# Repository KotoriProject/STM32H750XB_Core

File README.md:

# STM32 H750XBH6 核心板设计规划
## 设计理念
从STM32的F0、F1系列一路至今，到目前最为复杂的H750IBK6开发板、核心板的设计，逐渐认识到了单片机系统的设计思路。

在使用低性能单片机的情况下，通常最小系统的PCB layout只需要普通的两层即可。因此，在这种情况下，应当尽量采用**一体化设计**，既可以节省PCB成本，又无需考虑多个PCB之间的耦合设计。

但如果使用的是像H7这一类的**高性能芯片**，并且，这些芯片因为其封装、外部扩展ram等等，会导致最小系统的复杂度急剧提升，PCB layout通常都需要**4层甚至以上的设计**，此时，如果还像低性能单片机一样一体化设计，将核心系统和外围系统设计到一个PCB上，不仅会无故增加成本，并且每一个不同的项目需求的外围电路不尽相同，若更改外围电路则需要连同核心系统一起更改，将会**花费大量时间在重复设计核心系统上**。

因此，采用核心板+底板的设计方式应运而生。通过将核心系统单独设计成一块固定的PCB，并通过引出**具有通用性的接口**，可以使得核心系统**随意**搭配不同的底板（外围电路）。
## 设计目标
1. 通过设计该核心板和对应配套的底板，在实践中学习到相应的知识。
2. 设计出一款可以使用核心芯片所具有的广泛的外设接口、并核心自身又有搭载必要的**内存拓展空间**。
3. 利用设计出的核心板和底板，实现各种个人构想的项目。

## 硬件设计
### Power
参考ST官方给出的H7电源设计，STM32H750XBH6共有以下供电域：

1. dw
2. 123
3. 321
4. 313421414
5. 
123321414
### External Memory
### GPIO AFIO
### Debug Port
### Physical Port

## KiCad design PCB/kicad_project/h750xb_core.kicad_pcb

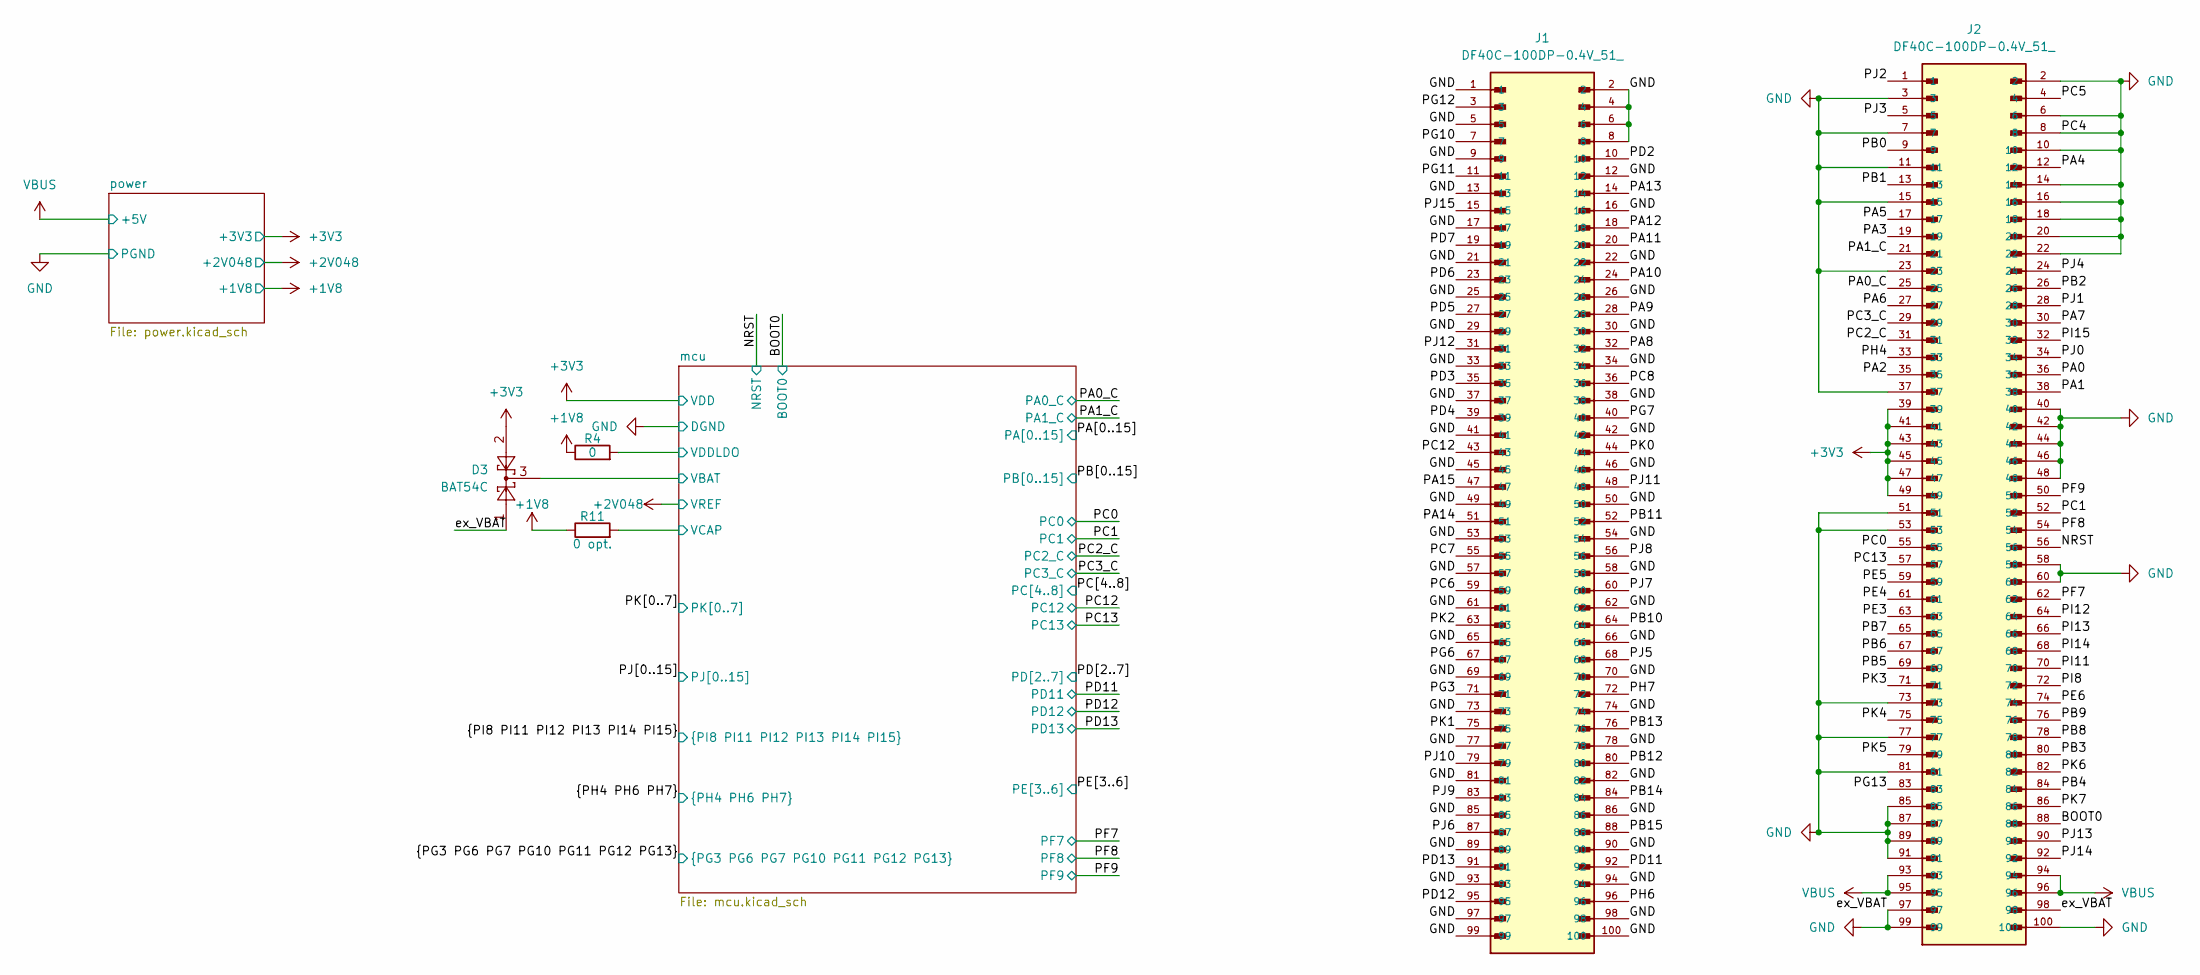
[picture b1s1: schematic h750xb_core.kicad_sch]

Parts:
D3: BAT54C; SOT-23
J1, J2: DF40C-100DP-0.4V_51_; HIROSE_DF40C-100DP-0.4V_51_; PARTREV 8
R4: 0; R_0603_1608Metric
R11: 0 opt.; R_0603_1608Metric

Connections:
+1V8: R4.1, R11.1; also elsewhere on the board
+3V3: D3.2, J2.39, J2.41, J2.43, J2.45, J2.47, J2.49; also elsewhere on the board
/BOOT0: J2.88; also elsewhere on the board
/NRST: J2.56; also elsewhere on the board
/PA0: J2.36; also elsewhere on the board
/PA0_C: J2.25; also elsewhere on the board
/PA1: J2.38; also elsewhere on the board
/PA1_C: J2.21; also elsewhere on the board
/PA2: J2.35; also elsewhere on the board
/PA3: J2.19; also elsewhere on the board
/PA4: J2.12; also elsewhere on the board
/PA5: J2.17; also elsewhere on the board
/PA6: J2.27; also elsewhere on the board
/PA7: J2.30; also elsewhere on the board
/PA8: J1.32; also elsewhere on the board
/PA9: J1.28; also elsewhere on the board
/PA10: J1.24; also elsewhere on the board
/PA11: J1.20; also elsewhere on the board
/PA12: J1.18; also elsewhere on the board
/PA13: J1.14; also elsewhere on the board
/PA14: J1.51; also elsewhere on the board
/PA15: J1.47; also elsewhere on the board
/PB0: J2.9; also elsewhere on the board
/PB1: J2.13; also elsewhere on the board
/PB2: J2.26; also elsewhere on the board
/PB3: J2.80; also elsewhere on the board
/PB4: J2.84; also elsewhere on the board
/PB5: J2.69; also elsewhere on the board
/PB6: J2.67; also elsewhere on the board
/PB7: J2.65; also elsewhere on the board
/PB8: J2.78; also elsewhere on the board
/PB9: J2.76; also elsewhere on the board
/PB10: J1.64; also elsewhere on the board
/PB11: J1.52; also elsewhere on the board
/PB12: J1.80; also elsewhere on the board
/PB13: J1.76; also elsewhere on the board
/PB14: J1.84; also elsewhere on the board
/PB15: J1.88; also elsewhere on the board
/PC0: J2.55; also elsewhere on the board
/PC1: J2.52; also elsewhere on the board
/PC2_C: J2.31; also elsewhere on the board
/PC3_C: J2.29; also elsewhere on the board
/PC5: J2.4; also elsewhere on the board
/PC6: J1.59; also elsewhere on the board
/PC7: J1.55; also elsewhere on the board
/PC8: J1.36; also elsewhere on the board
/PC12: J1.43; also elsewhere on the board
/PC13: J2.57; also elsewhere on the board
/PD2: J1.10; also elsewhere on the board
/PD3: J1.35; also elsewhere on the board
/PD4: J1.39; also elsewhere on the board
/PD5: J1.27; also elsewhere on the board
/PD6: J1.23; also elsewhere on the board
/PD7: J1.19; also elsewhere on the board
/PD11: J1.92; also elsewhere on the board
/PD12: J1.95; also elsewhere on the board
/PD13: J1.91; also elsewhere on the board
/PE3: J2.63; also elsewhere on the board
/PE4: J2.61; also elsewhere on the board
/PE5: J2.59; also elsewhere on the board
/PE6: J2.74; also elsewhere on the board
/PF7: J2.62; also elsewhere on the board
/PF8: J2.54; also elsewhere on the board
/PF9: J2.50; also elsewhere on the board
/PG3: J1.71; also elsewhere on the board
/PG6: J1.67; also elsewhere on the board
/PG7: J1.40; also elsewhere on the board
/PG10: J1.7; also elsewhere on the board
/PG11: J1.11; also elsewhere on the board
/PG12: J1.3; also elsewhere on the board
/PG13: J2.83; also elsewhere on the board
/PH4: J2.33; also elsewhere on the board
/PH6: J1.96; also elsewhere on the board
/PH7: J1.72; also elsewhere on the board
/PI8: J2.72; also elsewhere on the board
/PI11: J2.70; also elsewhere on the board
/PI12: J2.64; also elsewhere on the board
/PI13: J2.66; also elsewhere on the board
/PI14: J2.68; also elsewhere on the board
/PI15: J2.32; also elsewhere on the board
/PJ0: J2.34; also elsewhere on the board
/PJ1: J2.28; also elsewhere on the board
/PJ2: J2.1; also elsewhere on the board
/PJ3: J2.5; also elsewhere on the board
/PJ4: J2.24; also elsewhere on the board
/PJ5: J1.68; also elsewhere on the board
/PJ6: J1.87; also elsewhere on the board
/PJ7: J1.60; also elsewhere on the board
/PJ8: J1.56; also elsewhere on the board
/PJ9: J1.83; also elsewhere on the board
/PJ10: J1.79; also elsewhere on the board
/PJ11: J1.48; also elsewhere on the board
/PJ12: J1.31; also elsewhere on the board
/PJ13: J2.90; also elsewhere on the board
/PJ14: J2.92; also elsewhere on the board
/PJ15: J1.15; also elsewhere on the board
/PK0: J1.44; also elsewhere on the board
/PK1: J1.75; also elsewhere on the board
/PK2: J1.63; also elsewhere on the board
/PK3: J2.71; also elsewhere on the board
/PK4: J2.75; also elsewhere on the board
/PK5: J2.79; also elsewhere on the board
/PK6: J2.82; also elsewhere on the board
/PK7: J2.86; also elsewhere on the board
/mcu/VBAT: D3.3; also elsewhere on the board
/mcu/VCAP: R11.2; also elsewhere on the board
/mcu/VDDLDO: R4.2; also elsewhere on the board
GND: D3.1, J1.1, J1.2, J1.4, J1.5, J1.6, J1.8, J1.9, J1.12, J1.13, J1.16, J1.17, J1.21, J1.22, J1.25, J1.26, J1.29, J1.30, J1.33, J1.34, J1.37, J1.38, J1.41, J1.42, J1.45, J1.46, J1.49, J1.50, J1.53, J1.54, J1.57, J1.58, J1.61, J1.62, J1.65, J1.66, J1.69, J1.70, J1.73, J1.74, J1.77, J1.78, J1.81, J1.82, J1.85, J1.86, J1.89, J1.90, J1.93, J1.94, J1.97, J1.98, J1.99, J1.100, J2.2, J2.3, J2.6, J2.7, J2.8, J2.10, J2.11, J2.14, J2.15, J2.16, J2.18, J2.20, J2.22, J2.23, J2.37, J2.40, J2.42, J2.44, J2.46, J2.48, J2.51, J2.53, J2.58, J2.60, J2.73, J2.77, J2.81, J2.85, J2.87, J2.89, J2.91, J2.97, J2.98, J2.99, J2.100; also elsewhere on the board
VBUS: J2.93, J2.94, J2.95, J2.96; also elsewhere on the board

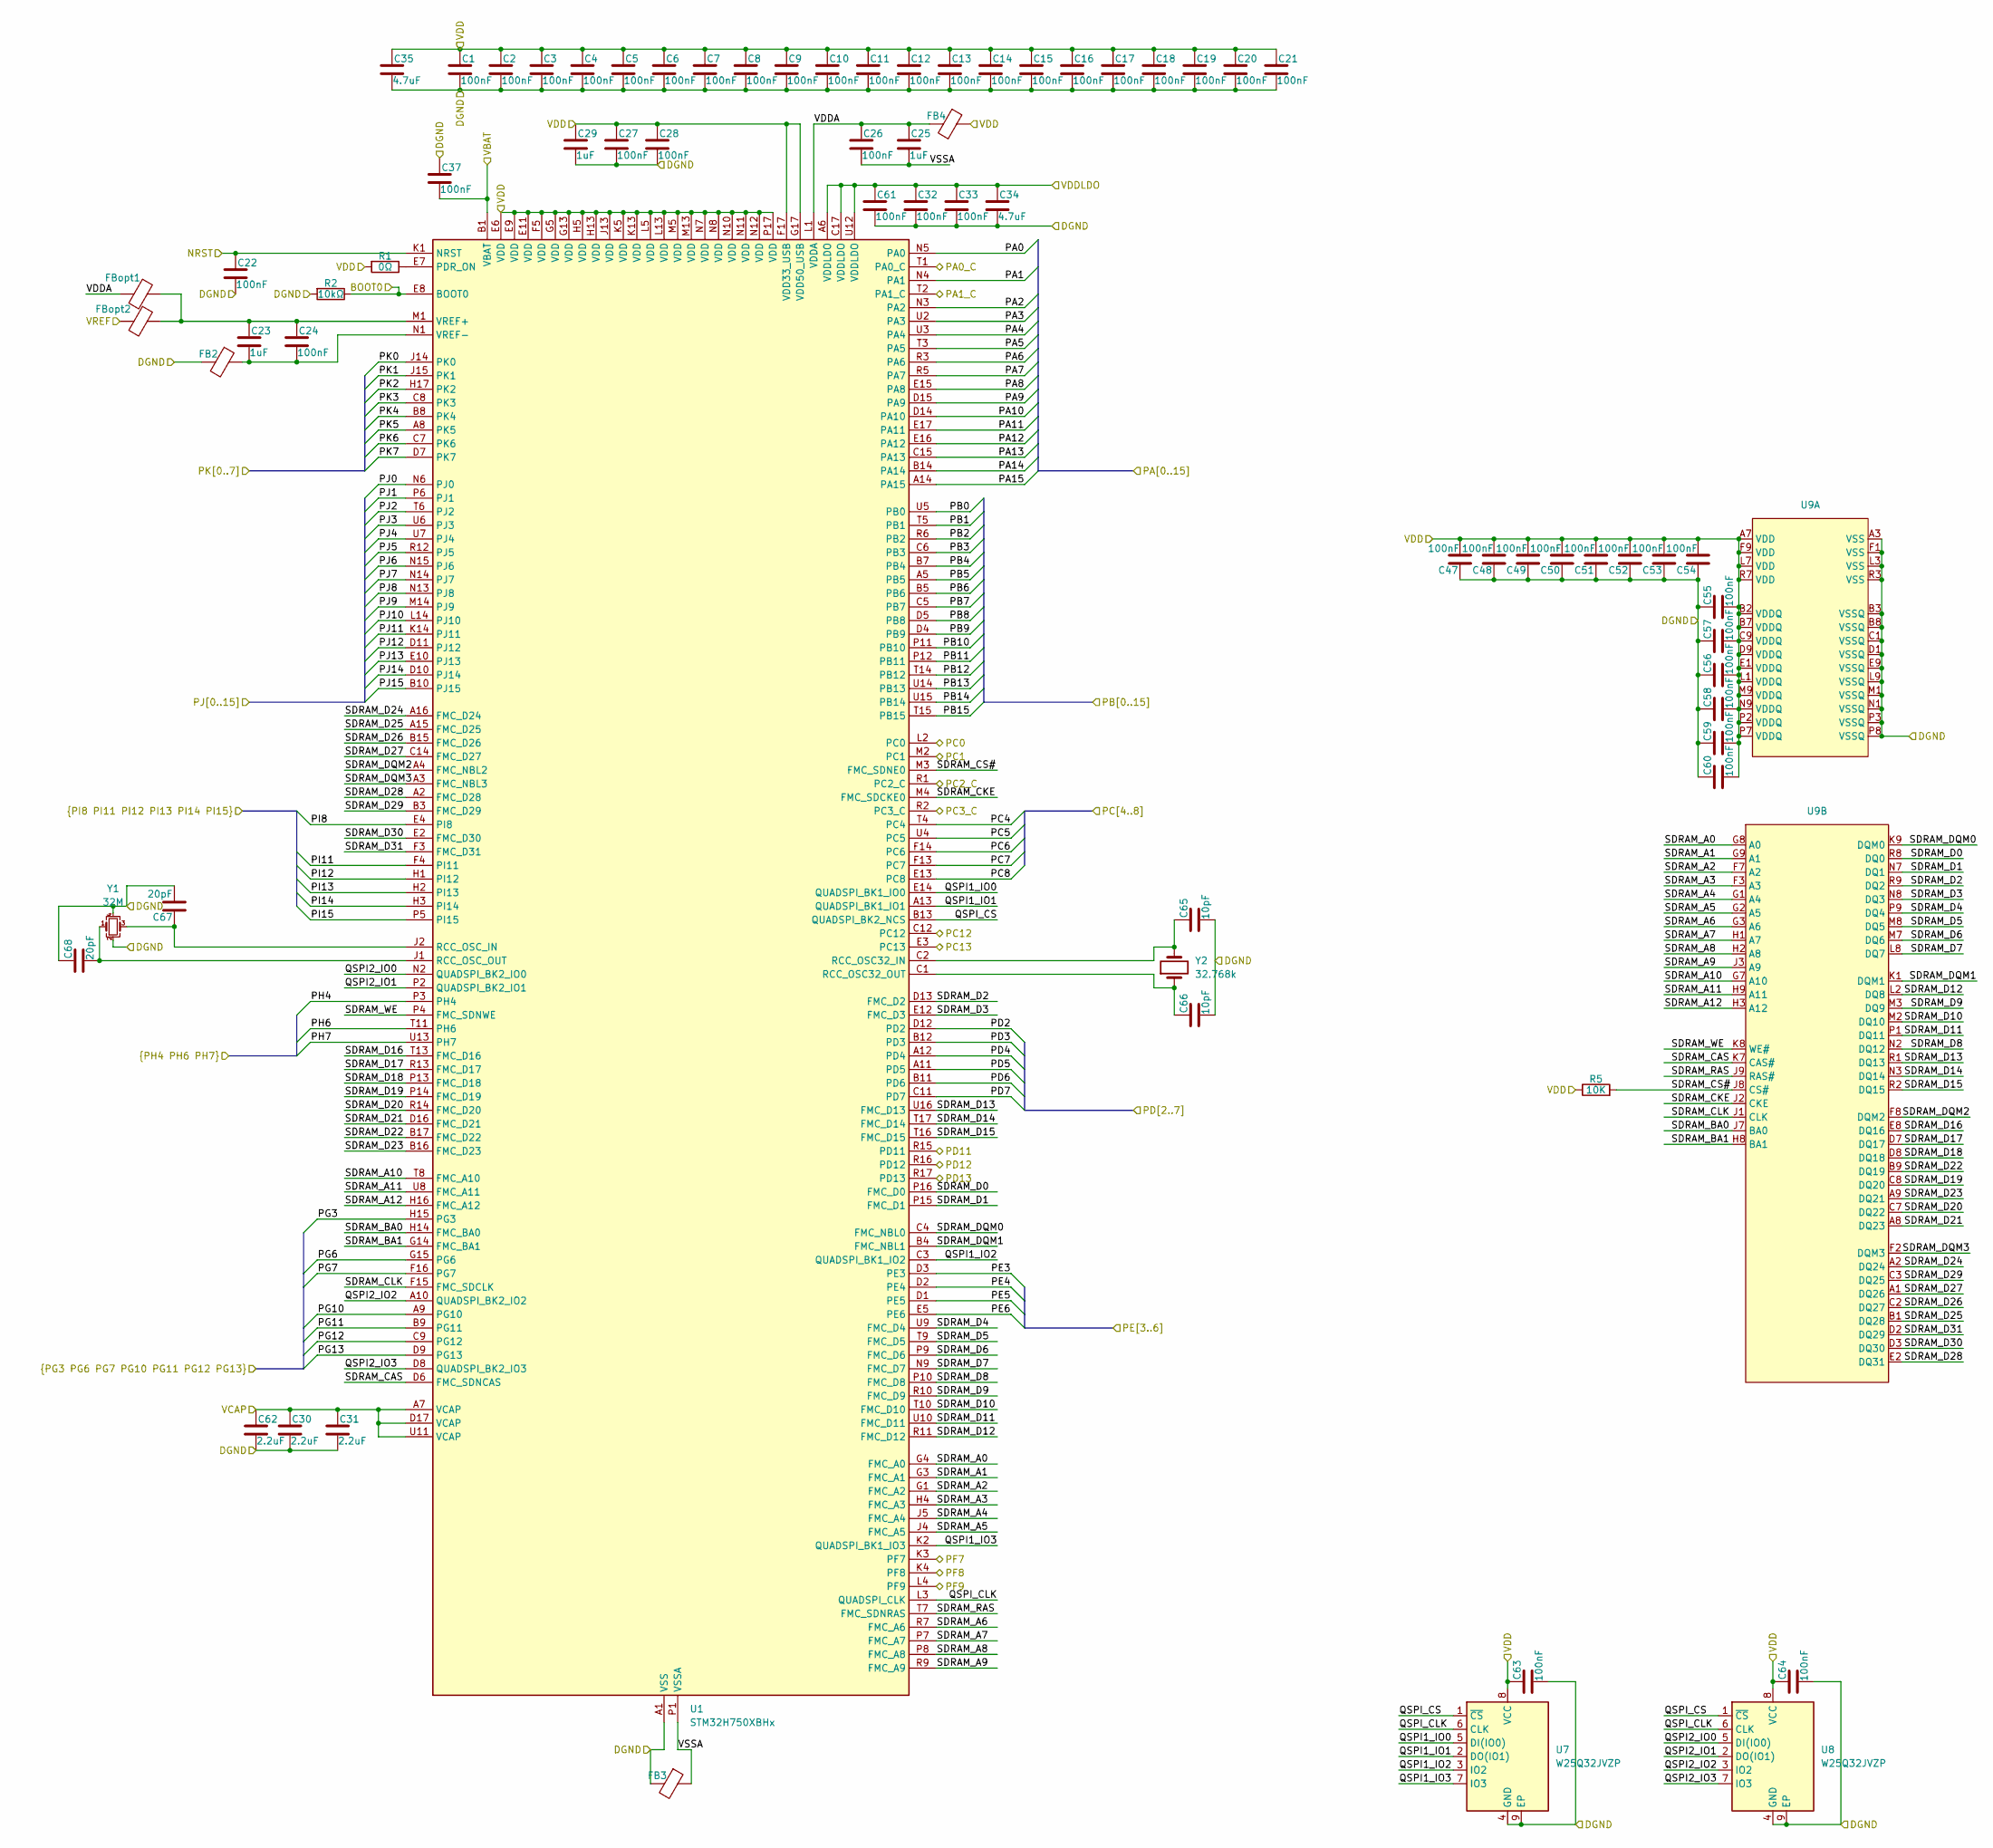
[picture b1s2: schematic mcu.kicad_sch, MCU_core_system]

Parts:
C1, C3, C4, C5, C6, C7, C8, C9, C10, C11, C12, C13, C14, C15, C17, C18, C19, C20, C21: 100nF; C_0201_0603Metric_Pad0.64x0.40mm_HandSolder
C2, C16, C22, C24, C26, C27, C28, C32, C33, C37, C47, C48, C49, C50, C51, C52, C53, C54, C55, C56, C57, C58, C59, C60, C61, C63, C64: 100nF; C_0402_1005Metric
C23, C25, C29: 1uF; C_0402_1005Metric
C30, C31, C62: 2.2uF; C_0402_1005Metric
C34, C35: 4.7uF; C_0402_1005Metric
C65, C66: 10pF; C_0402_1005Metric
C67, C68: 20pF; C_0402_1005Metric
FB2, FB3, FB4: 120Ω; L_0603_1608Metric; LCSC C14709
FBopt1, FBopt2: 120Ω; L_0603_1608Metric; LCSC C14709
R1: 0Ω; R_0402_1005Metric
R2: 10kΩ; R_0402_1005Metric
R5: 10K; R_0402_1005Metric
U1: STM32H750XBHx; TFBGA-265_14x14mm_Layout17x17_P0.8mm
U7, U8: W25Q32JVZP; WSON-8-1EP_6x5mm_P1.27mm_EP3.4x4.3mm
U9: BGA-90_8.0x13.0mm_Layout2x3x15_P0.8mm; Manufacturer Part IS42S32160F-7BLI; LCSC Part Name IS42S32160F-7BLI
Y1: 32M; Crystal_SMD_2016-4Pin_2.0x1.6mm; LCSC C2965582
Y2: 32.768k; Crystal_SMD_3215-2Pin_3.2x1.5mm; LCSC C48615

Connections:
+2V048: FBopt2.2; also elsewhere on the board
+3V3: C1.1, C2.1, C3.1, C4.1, C5.1, C6.1, C7.1, C8.1, C9.1, C10.1, C11.1, C12.1, C13.1, C14.1, C15.1, C16.1, C17.1, C18.1, C19.1, C20.1, C21.1, C27.1, C28.1, C29.1, C35.1, C47.2, C48.2, C49.2, C50.2, C51.2, C52.2, C53.2, C54.2, C55.2, C56.2, C57.2, C58.2, C59.2, C60.2, C63.1, C64.1, FB4.1, R1.2, R5.1, U1.E6 (VDD), U1.E9 (VDD), U1.E11 (VDD), U1.F5 (VDD), U1.F17 (VDD33_USB), U1.G5 (VDD), U1.G13 (VDD), U1.G17 (VDD50_USB), U1.H5 (VDD), U1.H13 (VDD), U1.J13 (VDD), U1.K5 (VDD), U1.K13 (VDD), U1.L5 (VDD), U1.L13 (VDD), U1.M5 (VDD), U1.M13 (VDD), U1.N7 (VDD), U1.N8 (VDD), U1.N10 (VDD), U1.N11 (VDD), U1.N12 (VDD), U1.P17 (VDD), U7.8 (VCC), U8.8 (VCC), U9.A7 (VDD), U9.B2 (VDDQ), U9.B7 (VDDQ), U9.C9 (VDDQ), U9.D9 (VDDQ), U9.E1 (VDDQ), U9.F9 (VDD), U9.L1 (VDDQ), U9.L7 (VDD), U9.M9 (VDDQ), U9.N9 (VDDQ), U9.P2 (VDDQ), U9.P7 (VDDQ), U9.R7 (VDD); also elsewhere on the board
/BOOT0: R2.1, U1.E8 (BOOT0); also elsewhere on the board
/NRST: C22.1, U1.K1 (NRST); also elsewhere on the board
/PA0: U1.N5 (PA0); also elsewhere on the board
/PA0_C: U1.T1 (PA0_C); also elsewhere on the board
/PA1: U1.N4 (PA1); also elsewhere on the board
/PA1_C: U1.T2 (PA1_C); also elsewhere on the board
/PA2: U1.N3 (PA2); also elsewhere on the board
/PA3: U1.U2 (PA3); also elsewhere on the board
/PA4: U1.U3 (PA4); also elsewhere on the board
/PA5: U1.T3 (PA5); also elsewhere on the board
/PA6: U1.R3 (PA6); also elsewhere on the board
/PA7: U1.R5 (PA7); also elsewhere on the board
/PA8: U1.E15 (PA8); also elsewhere on the board
/PA9: U1.D15 (PA9); also elsewhere on the board
/PA10: U1.D14 (PA10); also elsewhere on the board
/PA11: U1.E17 (PA11); also elsewhere on the board
/PA12: U1.E16 (PA12); also elsewhere on the board
/PA13: U1.C15 (PA13); also elsewhere on the board
/PA14: U1.B14 (PA14); also elsewhere on the board
/PA15: U1.A14 (PA15); also elsewhere on the board
/PB0: U1.U5 (PB0); also elsewhere on the board
/PB1: U1.T5 (PB1); also elsewhere on the board
/PB2: U1.R6 (PB2); also elsewhere on the board
/PB3: U1.C6 (PB3); also elsewhere on the board
/PB4: U1.B7 (PB4); also elsewhere on the board
/PB5: U1.A5 (PB5); also elsewhere on the board
/PB6: U1.B5 (PB6); also elsewhere on the board
/PB7: U1.C5 (PB7); also elsewhere on the board
/PB8: U1.D5 (PB8); also elsewhere on the board
/PB9: U1.D4 (PB9); also elsewhere on the board
/PB10: U1.P11 (PB10); also elsewhere on the board
/PB11: U1.P12 (PB11); also elsewhere on the board
/PB12: U1.T14 (PB12); also elsewhere on the board
/PB13: U1.U14 (PB13); also elsewhere on the board
/PB14: U1.U15 (PB14); also elsewhere on the board
/PB15: U1.T15 (PB15); also elsewhere on the board
/PC0: U1.L2 (PC0); also elsewhere on the board
/PC1: U1.M2 (PC1); also elsewhere on the board
/PC2_C: U1.R1 (PC2_C); also elsewhere on the board
/PC3_C: U1.R2 (PC3_C); also elsewhere on the board
/PC5: U1.U4 (PC5); also elsewhere on the board
/PC6: U1.F14 (PC6); also elsewhere on the board
/PC7: U1.F13 (PC7); also elsewhere on the board
/PC8: U1.E13 (PC8); also elsewhere on the board
/PC12: U1.C12; also elsewhere on the board
/PC13: U1.E3 (PC13); also elsewhere on the board
/PD2: U1.D12 (PD2); also elsewhere on the board
/PD3: U1.B12 (PD3); also elsewhere on the board
/PD4: U1.A12 (PD4); also elsewhere on the board
/PD5: U1.A11 (PD5); also elsewhere on the board
/PD6: U1.B11 (PD6); also elsewhere on the board
/PD7: U1.C11 (PD7); also elsewhere on the board
/PD11: U1.R15 (PD11); also elsewhere on the board
/PD12: U1.R16 (PD12); also elsewhere on the board
/PD13: U1.R17 (PD13); also elsewhere on the board
/PE3: U1.D3 (PE3); also elsewhere on the board
/PE4: U1.D2 (PE4); also elsewhere on the board
/PE5: U1.D1 (PE5); also elsewhere on the board
/PE6: U1.E5 (PE6); also elsewhere on the board
/PF7: U1.K3 (PF7); also elsewhere on the board
/PF8: U1.K4 (PF8); also elsewhere on the board
/PF9: U1.L4 (PF9); also elsewhere on the board
/PG3: U1.H15 (PG3); also elsewhere on the board
/PG6: U1.G15 (PG6); also elsewhere on the board
/PG7: U1.F16 (PG7); also elsewhere on the board
/PG10: U1.A9 (PG10); also elsewhere on the board
/PG11: U1.B9 (PG11); also elsewhere on the board
/PG12: U1.C9 (PG12); also elsewhere on the board
/PG13: U1.D9 (PG13); also elsewhere on the board
/PH4: U1.P3 (PH4); also elsewhere on the board
/PH6: U1.T11 (PH6); also elsewhere on the board
/PH7: U1.U13 (PH7); also elsewhere on the board
/PI8: U1.E4 (PI8); also elsewhere on the board
/PI11: U1.F4 (PI11); also elsewhere on the board
/PI12: U1.H1 (PI12); also elsewhere on the board
/PI13: U1.H2 (PI13); also elsewhere on the board
/PI14: U1.H3 (PI14); also elsewhere on the board
/PI15: U1.P5 (PI15); also elsewhere on the board
/PJ0: U1.N6 (PJ0); also elsewhere on the board
/PJ1: U1.P6 (PJ1); also elsewhere on the board
/PJ2: U1.T6 (PJ2); also elsewhere on the board
/PJ3: U1.U6 (PJ3); also elsewhere on the board
/PJ4: U1.U7 (PJ4); also elsewhere on the board
/PJ5: U1.R12 (PJ5); also elsewhere on the board
/PJ6: U1.N15 (PJ6); also elsewhere on the board
/PJ7: U1.N14 (PJ7); also elsewhere on the board
/PJ8: U1.N13 (PJ8); also elsewhere on the board
/PJ9: U1.M14 (PJ9); also elsewhere on the board
/PJ10: U1.L14 (PJ10); also elsewhere on the board
/PJ11: U1.K14 (PJ11); also elsewhere on the board
/PJ12: U1.D11 (PJ12); also elsewhere on the board
/PJ13: U1.E10 (PJ13); also elsewhere on the board
/PJ14: U1.D10 (PJ14); also elsewhere on the board
/PJ15: U1.B10 (PJ15); also elsewhere on the board
/PK0: U1.J14 (PK0); also elsewhere on the board
/PK1: U1.J15 (PK1); also elsewhere on the board
/PK2: U1.H17 (PK2); also elsewhere on the board
/PK3: U1.C8 (PK3); also elsewhere on the board
/PK4: U1.B8 (PK4); also elsewhere on the board
/PK5: U1.A8 (PK5); also elsewhere on the board
/PK6: U1.C7 (PK6); also elsewhere on the board
/PK7: U1.D7 (PK7); also elsewhere on the board
/mcu/QSPI1_IO0: U1.E14 (QUADSPI_BK1_IO0), U7.5 (DI(IO0))
/mcu/QSPI1_IO1: U1.A13 (QUADSPI_BK1_IO1), U7.2 (DO(IO1))
/mcu/QSPI1_IO2: U1.C3 (QUADSPI_BK1_IO2), U7.3 (IO2)
/mcu/QSPI1_IO3: U1.K2 (QUADSPI_BK1_IO3), U7.7 (IO3)
/mcu/QSPI2_IO0: U1.N2 (QUADSPI_BK2_IO0), U8.5 (DI(IO0))
/mcu/QSPI2_IO1: U1.P2 (QUADSPI_BK2_IO1), U8.2 (DO(IO1))
/mcu/QSPI2_IO2: U1.A10 (QUADSPI_BK2_IO2), U8.3 (IO2)
/mcu/QSPI2_IO3: U1.D8 (QUADSPI_BK2_IO3), U8.7 (IO3)
/mcu/QSPI_CLK: U1.L3 (QUADSPI_CLK), U7.6 (CLK), U8.6 (CLK)
/mcu/QSPI_CS: U1.B13 (QUADSPI_BK2_NCS), U7.1 (~CS), U8.1 (~CS)
/mcu/SDRAM_A0: U1.G4 (FMC_A0), U9.G8 (A0)
/mcu/SDRAM_A1: U1.G3 (FMC_A1), U9.G9 (A1)
/mcu/SDRAM_A2: U1.G1 (FMC_A2), U9.F7 (A2)
/mcu/SDRAM_A3: U1.H4 (FMC_A3), U9.F3 (A3)
/mcu/SDRAM_A4: U1.J5 (FMC_A4), U9.G1 (A4)
/mcu/SDRAM_A5: U1.J4 (FMC_A5), U9.G2 (A5)
/mcu/SDRAM_A6: U1.R7 (FMC_A6), U9.G3 (A6)
/mcu/SDRAM_A7: U1.P7 (FMC_A7), U9.H1 (A7)
/mcu/SDRAM_A8: U1.P8 (FMC_A8), U9.H2 (A8)
/mcu/SDRAM_A9: U1.R9 (FMC_A9), U9.J3 (A9)
/mcu/SDRAM_A10: U1.T8 (FMC_A10), U9.G7 (A10)
/mcu/SDRAM_A11: U1.U8 (FMC_A11), U9.H9 (A11)
/mcu/SDRAM_A12: U1.H16 (FMC_A12), U9.H3 (A12)
/mcu/SDRAM_BA0: U1.H14 (FMC_BA0), U9.J7 (BA0)
/mcu/SDRAM_BA1: U1.G14 (FMC_BA1), U9.H8 (BA1)
/mcu/SDRAM_CAS: U1.D6 (FMC_SDNCAS), U9.K7 (CAS#)
/mcu/SDRAM_CKE: U1.M4 (FMC_SDCKE0), U9.J2 (CKE)
/mcu/SDRAM_CLK: U1.F15 (FMC_SDCLK), U9.J1 (CLK)
/mcu/SDRAM_CS#: R5.2, U1.M3 (FMC_SDNE0), U9.J8 (CS#)
/mcu/SDRAM_D0: U1.P16 (FMC_D0), U9.R8 (DQ0)
/mcu/SDRAM_D1: U1.P15 (FMC_D1), U9.N7 (DQ1)
/mcu/SDRAM_D2: U1.D13 (FMC_D2), U9.R9 (DQ2)
/mcu/SDRAM_D3: U1.E12 (FMC_D3), U9.N8 (DQ3)
/mcu/SDRAM_D4: U1.U9 (FMC_D4), U9.P9 (DQ4)
/mcu/SDRAM_D5: U1.T9 (FMC_D5), U9.M8 (DQ5)
/mcu/SDRAM_D6: U1.P9 (FMC_D6), U9.M7 (DQ6)
/mcu/SDRAM_D7: U1.N9 (FMC_D7), U9.L8 (DQ7)
/mcu/SDRAM_D8: U1.P10 (FMC_D8), U9.N2 (DQ12)
/mcu/SDRAM_D9: U1.R10 (FMC_D9), U9.M3 (DQ9)
/mcu/SDRAM_D10: U1.T10 (FMC_D10), U9.M2 (DQ10)
/mcu/SDRAM_D11: U1.U10 (FMC_D11), U9.P1 (DQ11)
/mcu/SDRAM_D12: U1.R11 (FMC_D12), U9.L2 (DQ8)
/mcu/SDRAM_D13: U1.U16 (FMC_D13), U9.R1 (DQ13)
/mcu/SDRAM_D14: U1.T17 (FMC_D14), U9.N3 (DQ14)
/mcu/SDRAM_D15: U1.T16 (FMC_D15), U9.R2 (DQ15)
/mcu/SDRAM_D16: U1.T13 (FMC_D16), U9.E8 (DQ16)
/mcu/SDRAM_D17: U1.R13 (FMC_D17), U9.D7 (DQ17)
/mcu/SDRAM_D18: U1.P13 (FMC_D18), U9.D8 (DQ18)
/mcu/SDRAM_D19: U1.P14 (FMC_D19), U9.C8 (DQ20)
/mcu/SDRAM_D20: U1.R14 (FMC_D20), U9.C7 (DQ22)
/mcu/SDRAM_D21: U1.D16 (FMC_D21), U9.A8 (DQ23)
/mcu/SDRAM_D22: U1.B17 (FMC_D22), U9.B9 (DQ19)
/mcu/SDRAM_D23: U1.B16 (FMC_D23), U9.A9 (DQ21)
/mcu/SDRAM_D24: U1.A16 (FMC_D24), U9.A2 (DQ24)
/mcu/SDRAM_D25: U1.A15 (FMC_D25), U9.B1 (DQ28)
/mcu/SDRAM_D26: U1.B15 (FMC_D26), U9.C2 (DQ27)
/mcu/SDRAM_D27: U1.C14 (FMC_D27), U9.A1 (DQ26)
/mcu/SDRAM_D28: U1.A2 (FMC_D28), U9.E2 (DQ31)
/mcu/SDRAM_D29: U1.B3 (FMC_D29), U9.C3 (DQ25)
/mcu/SDRAM_D30: U1.E2 (FMC_D30), U9.D3 (DQ30)
/mcu/SDRAM_D31: U1.F3 (FMC_D31), U9.D2 (DQ29)
/mcu/SDRAM_DQM0: U1.C4 (FMC_NBL0), U9.K9 (DQM0)
/mcu/SDRAM_DQM1: U1.B4 (FMC_NBL1), U9.K1 (DQM1)
/mcu/SDRAM_DQM2: U1.A4 (FMC_NBL2), U9.F8 (DQM2)
/mcu/SDRAM_DQM3: U1.A3 (FMC_NBL3), U9.F2 (DQM3)
/mcu/SDRAM_RAS: U1.T7 (FMC_SDNRAS), U9.J9 (RAS#)
/mcu/SDRAM_WE: U1.P4 (FMC_SDNWE), U9.K8 (WE#)
/mcu/VBAT: C37.2, U1.B1 (VBAT); also elsewhere on the board
/mcu/VCAP: C30.1, C31.1, C62.1, U1.A7 (VCAP), U1.D17 (VCAP), U1.U11 (VCAP); also elsewhere on the board
/mcu/VDDA: C25.1, C26.1, FB4.2, FBopt1.2, U1.L1 (VDDA)
/mcu/VDDLDO: C32.1, C33.1, C34.1, C61.1, U1.A6 (VDDLDO), U1.C17 (VDDLDO), U1.U12 (VDDLDO); also elsewhere on the board
/mcu/VSSA: C25.2, C26.2, FB3.1, U1.P1 (VSSA)
GND: C1.2, C2.2, C3.2, C4.2, C5.2, C6.2, C7.2, C8.2, C9.2, C10.2, C11.2, C12.2, C13.2, C14.2, C15.2, C16.2, C17.2, C18.2, C19.2, C20.2, C21.2, C22.2, C27.2, C28.2, C29.2, C30.2, C31.2, C32.2, C33.2, C34.2, C35.2, C37.1, C47.1, C48.1, C49.1, C50.1, C51.1, C52.1, C53.1, C54.1, C55.1, C56.1, C57.1, C58.1, C59.1, C60.1, C61.2, C62.2, C63.2, C64.2, C65.2, C66.2, C67.2, C68.1, FB2.2, FB3.2, R2.2, U1.A1 (VSS), U1.A17 (VSS), U1.B2 (VSS), U1.B6 (VSS), U1.C10 (VSS), U1.C13 (VSS), U1.C16 (VSS), U1.F1 (VSS), U1.F2 (VSS), U1.G2 (VSS), U1.G7 (VSS), U1.G8 (VSS), U1.G9 (VSS), U1.G10 (VSS), U1.G11 (VSS), U1.G16 (VSS), U1.H7 (VSS), U1.H8 (VSS), U1.H9 (VSS), U1.H10 (VSS), U1.H11 (VSS), U1.J3 (VSS), U1.J7 (VSS), U1.J8 (VSS), U1.J9 (VSS), U1.J10 (VSS), U1.J11 (VSS), U1.J16 (VSS), U1.J17 (VSS), U1.K7 (VSS), U1.K8 (VSS), U1.K9 (VSS), U1.K10 (VSS), U1.K11 (VSS), U1.K15 (VSS), U1.L7 (VSS), U1.L8 (VSS), U1.L9 (VSS), U1.L10 (VSS), U1.L11 (VSS), U1.L15 (VSS), U1.M15 (VSS), U1.N16 (VSS), U1.R4 (VSS), U1.R8 (VSS), U1.T4 (PC4), U1.T12 (VSS), U1.U1 (VSS), U1.U17 (VSS), U7.4 (GND), U7.9 (EP), U8.4 (GND), U8.9 (EP), U9.A3 (VSS), U9.B3 (VSSQ), U9.B8 (VSSQ), U9.C1 (VSSQ), U9.D1 (VSSQ), U9.E9 (VSSQ), U9.F1 (VSS), U9.L3 (VSS), U9.L9 (VSSQ), U9.M1 (VSSQ), U9.N1 (VSSQ), U9.P3 (VSSQ), U9.P8 (VSSQ), U9.R3 (VSS), Y1.2, Y1.4; also elsewhere on the board
unnamed: C65.1, U1.C2 (RCC_OSC32_IN), Y2.2
unnamed: C66.1, U1.C1 (RCC_OSC32_OUT), Y2.1
unnamed: R1.1, U1.E7 (PDR_ON)
unnamed: C67.1, U1.J2 (RCC_OSC_IN), Y1.3
unnamed: C68.2, U1.J1 (RCC_OSC_OUT), Y1.1
unnamed: C23.1, C24.1, FBopt1.1, FBopt2.1, U1.M1 (VREF+)
unnamed: C23.2, C24.2, FB2.1, U1.N1 (VREF-)

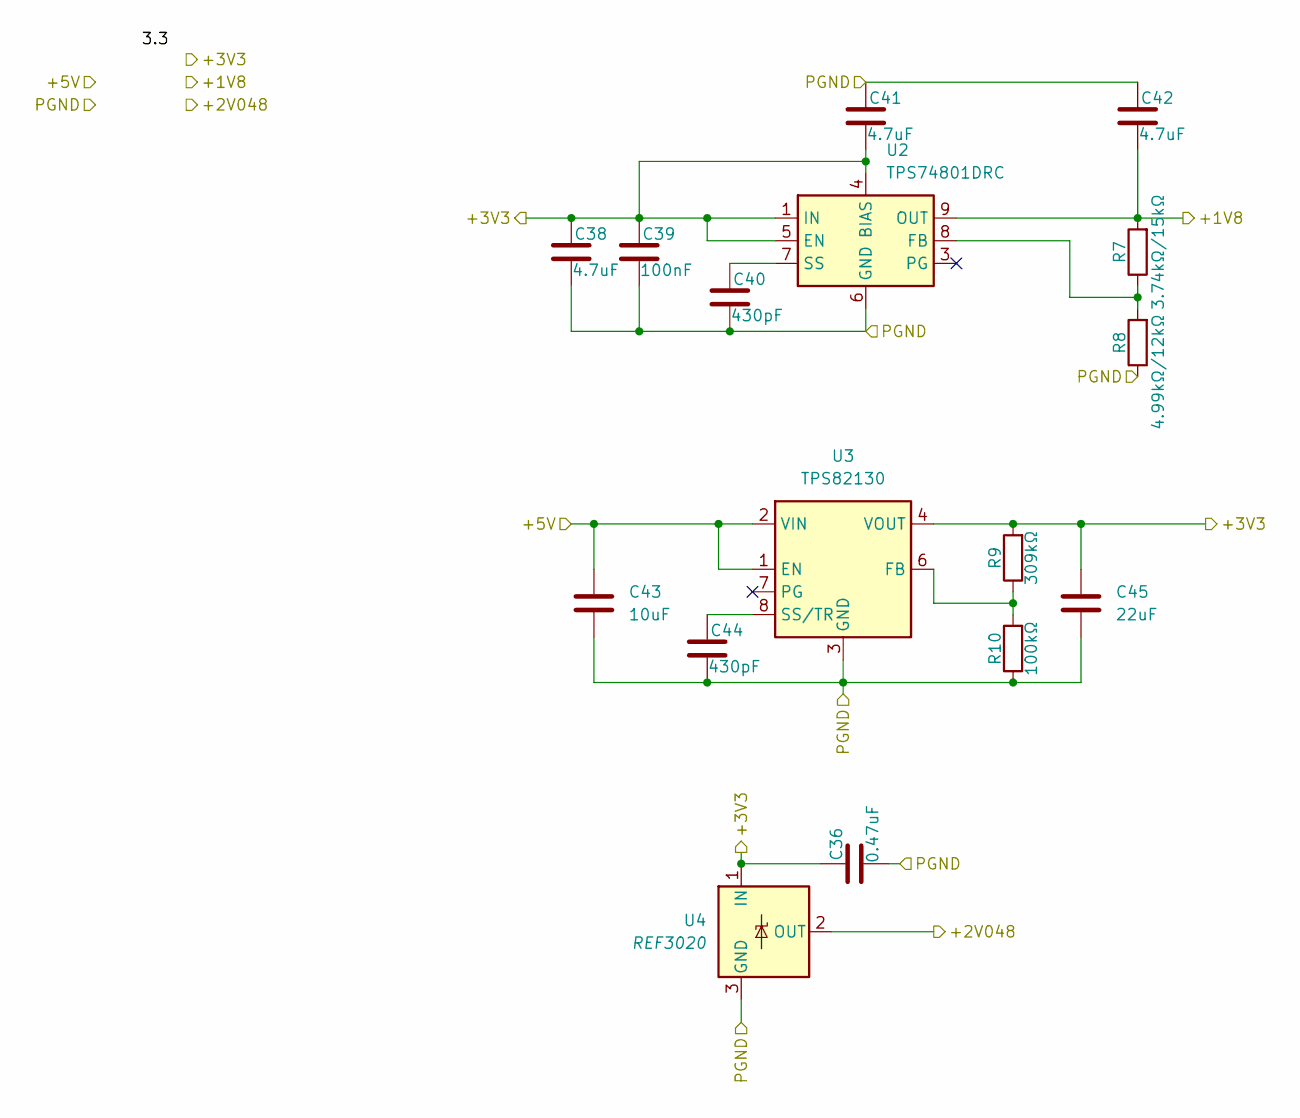
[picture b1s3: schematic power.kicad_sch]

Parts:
C36: 0.47uF; C_0402_1005Metric
C38, C41, C42: 4.7uF; C_0402_1005Metric
C39: 100nF; C_0402_1005Metric
C40, C44: 430pF; C_0402_1005Metric
C43: 10uF; C_0603_1608Metric
C45: 22uF; C_0603_1608Metric; LCSC C415703
R7: 3.74kΩ/15kΩ; R_0402_1005Metric
R8: 4.99kΩ/12kΩ; R_0402_1005Metric
R9: 309kΩ; R_0402_1005Metric
R10: 100kΩ; R_0402_1005Metric
U2: TPS74801DRC; VSON-10-1EP_3x3mm_P0.5mm_EP1.65x2.4mm_ThermalVias
U3: TPS82130; Texas_SIL0008D_MicroSiP-8-1EP_2.8x3mm_P0.65mm_EP1.1x1.9mm_T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
U4: REF3020; SOT-23

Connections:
+1V8: C42.2, R7.2, U2.9 (OUT), U2.10 (OUT); also elsewhere on the board
+2V048: U4.2 (OUT); also elsewhere on the board
+3V3: C36.1, C38.1, C39.1, C41.2, C45.1, R9.2, U2.1 (IN), U2.2 (IN), U2.4 (BIAS), U2.5 (EN), U3.4 (VOUT), U3.5 (VOUT), U4.1 (IN); also elsewhere on the board
GND: C36.2, C38.2, C39.2, C40.2, C41.1, C42.1, C43.2, C44.2, C45.2, R8.1, R10.1, U2.6 (GND), U2.11 (GND), U3.3 (GND), U3.9 (GND), U4.3 (GND); also elsewhere on the board
unnamed: R7.1, R8.2, U2.8 (FB)
unnamed: C40.1, U2.7 (SS)
unnamed: R9.1, R10.2, U3.6 (FB)
unnamed: C44.1, U3.8 (SS/TR)
VBUS: C43.1, U3.1 (EN), U3.2 (VIN); also elsewhere on the board

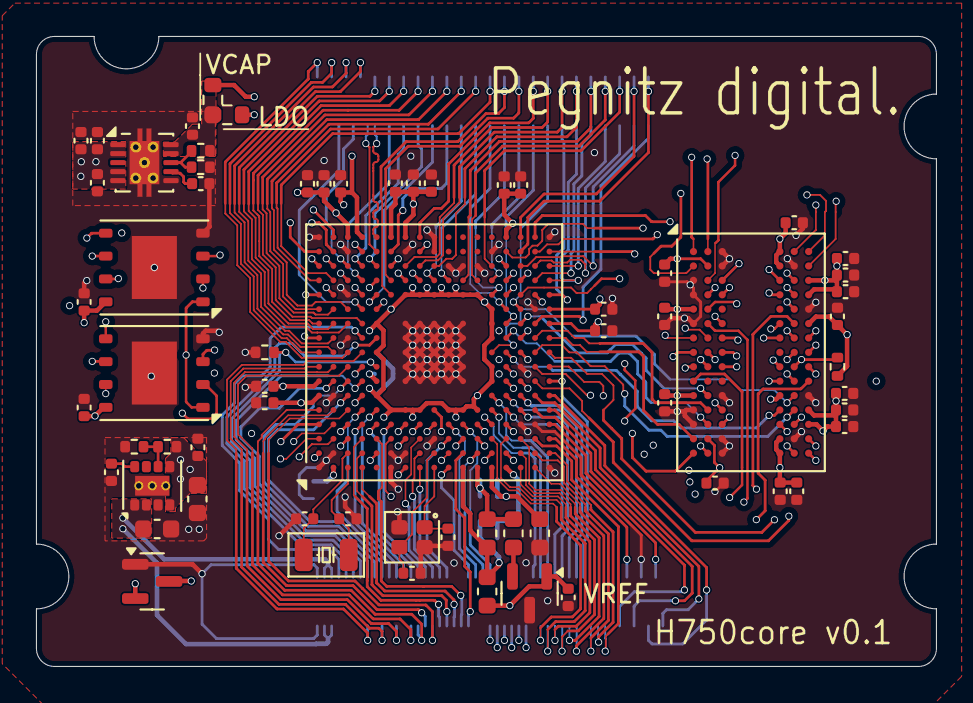
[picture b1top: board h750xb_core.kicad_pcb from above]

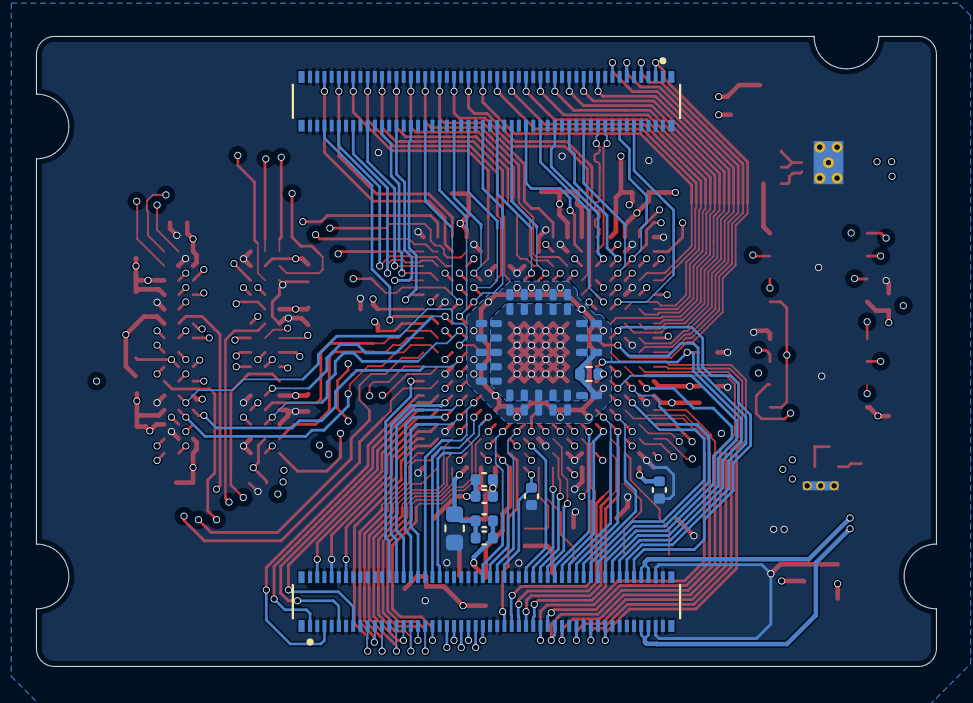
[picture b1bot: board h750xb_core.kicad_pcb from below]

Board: 6 copper layers, 50.0 x 35.0 mm, 93 parts (29 on the bottom side), 190 nets.

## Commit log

2024-06-10 upload
2024-06-10 test
2024-06-10 test2
2024-06-16 TPS82130 fb
2024-07-01 更新物料 删除16bit sdram*2 改为32bit sdram*1
2024-07-06 MCU部分扇出，SDRAM走线ing
2024-07-08 绕走SDRAM走线。。因复杂度太高，放弃做等长 目前差最后几根数据线，可视情况交换线序
2024-07-10 完成了SDRAM和QSPI的走线，QSPI做了网络等长匹配（两根复用线未连接以用于准确计算线长）
2024-07-11 铺铜，增加BTB
2024-07-11 为什么又不能用git！！！！！！！
2024-07-17 更新原理图网络和PCB部分IO走线
2024-07-18 完工0-0
2024-07-19 导出gerber
2024-08-05 失能部分不使用的外设
